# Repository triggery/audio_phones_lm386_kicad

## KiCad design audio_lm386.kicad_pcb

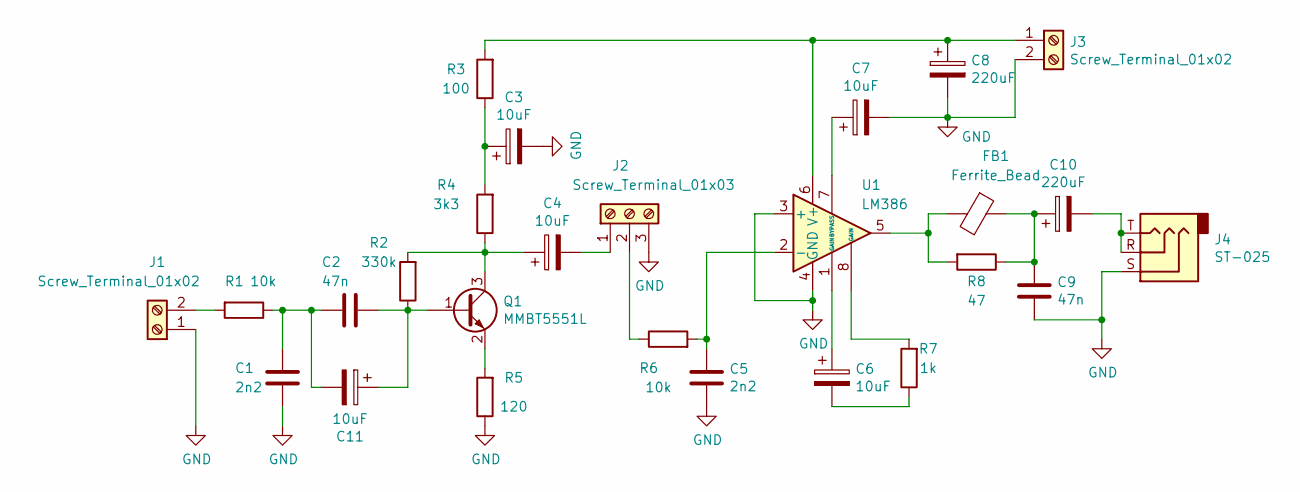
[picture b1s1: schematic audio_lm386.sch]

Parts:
C1, C5: 2n2; C_0805_2012Metric; PartNumber 0805-2.2nF 50V
C2, C9: 47n; C_0805_2012Metric; ManufacturePartNumber GRM21BR72A473KA01L
C3, C4, C6, C7, C11: 10uF; C_1206_3216Metric
C8: 220uF; CP_Radial_D5.0mm_P2.50mm
C10: 220uF; CP_Radial_D6.3mm_P2.50mm
FB1: Ferrite_Bead; R_0805_2012Metric
J1, J3: Screw_Terminal_01x02; PinHeader_1x02_P2.54mm_Vertical
J2: Screw_Terminal_01x03; PinHeader_1x03_P2.54mm_Vertical
J4: ST-025; ST-025 audio_jack
Q1: MMBT5551L; SOT-23
R1, R6: 10k; R_0805_2012Metric
R2: 330k; R_0805_2012Metric
R3: 100; R_0805_2012Metric
R4: 3k3; R_0805_2012Metric
R5: 120; R_0805_2012Metric
R7: 1k; R_0805_2012Metric
R8: 47; R_0805_2012Metric
U1: LM386; SOIC-8_3.9x4.9mm_P1.27mm

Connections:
GND: C1.2, C3.2, C5.2, C7.2, C8.2, C9.2, J1.1, J2.3, J3.2, J4.S, R5.1, U1.3 (+), U1.4 (GND)
unnamed: C1.1, C2.2, C11.2, R1.1
unnamed: C3.1, R3.1, R4.2
unnamed: C4.1, Q1.3 (C), R2.2, R4.1
unnamed: C4.2, J2.1
unnamed: C5.1, R6.2, U1.2 (-)
unnamed: C6.1, U1.1 (GAIN)
unnamed: C6.2, R7.1
unnamed: C7.1, U1.7 (BYPASS)
unnamed: C8.1, J3.1, R3.2, U1.6 (V+)
unnamed: C9.1, C10.1, FB1.1, R8.1
unnamed: C10.2, J4.R, J4.T
unnamed: C2.1, C11.1, Q1.1 (B), R2.1
unnamed: FB1.2, R8.2, U1.5
unnamed: J1.2, R1.2
unnamed: J2.2, R6.1
unnamed: Q1.2 (E), R5.2
unnamed: R7.2, U1.8 (GAIN)

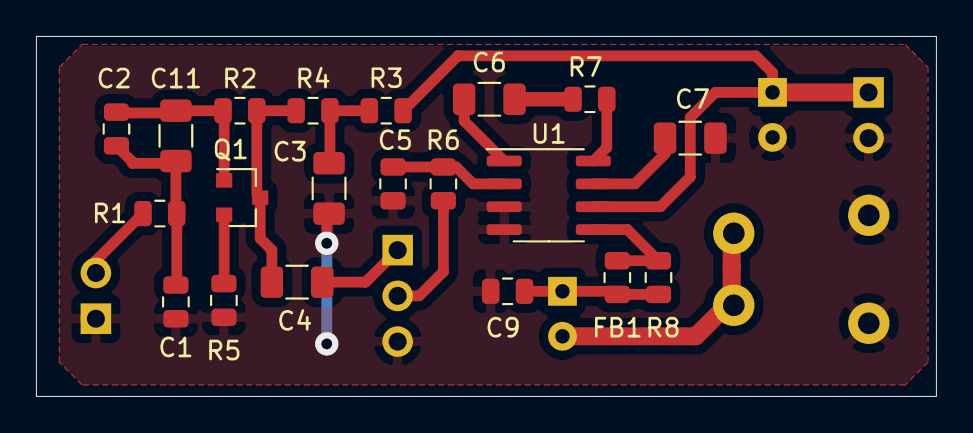
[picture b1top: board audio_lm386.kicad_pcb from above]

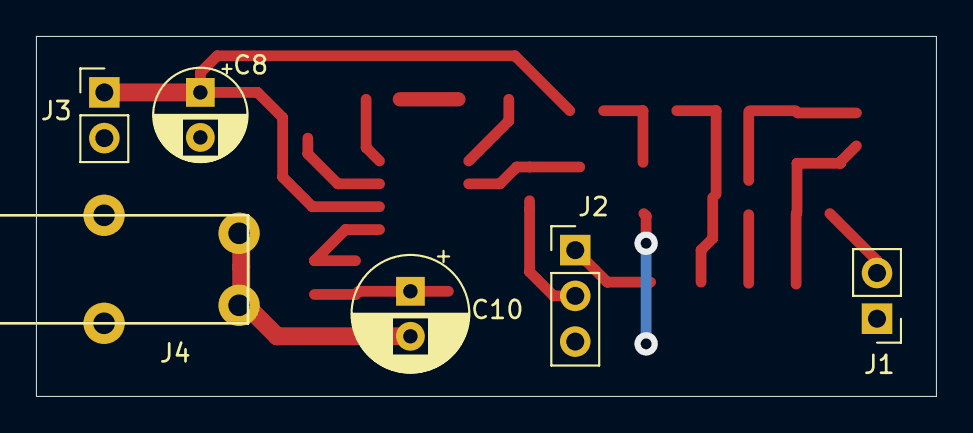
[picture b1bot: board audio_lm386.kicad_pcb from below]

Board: 2 copper layers, 50.0 x 20.0 mm, 26 parts (6 on the bottom side), 18 nets.

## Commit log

2020-01-11 add README
2020-01-26 kicad libs changed
2020-01-26 добавлен предусилитель с пинами для подключения потенциометра
2020-01-26 выполнена трассировка для предусилителя с пинами для подключения потенциометра
